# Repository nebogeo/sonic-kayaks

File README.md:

Sonic Kayak
===========

Originally based on the [Sonic Bikes](https://github.com/sonicbikes/)
system, a Raspberry Pi based citizen science project where kayaks
become musical & scientific instruments for investigating the marine
world.

We've added new sensors for citizen science data collection purposes:

* Thermometer
* Air pollution (particulate matter)
* Custom turbidity sensor
* Hydrophone

The system uses Pure Data for live audio sonification.

See the [Wiki](https://github.com/fo-am/sonic-kayaks/wiki) for full documentation on how to build a Sonic Kayak.

More installation instructions for the Raspberry Pi can be found here:
https://github.com/sonicbikes/sonic-bike-init

Hardware License
----------------

Sonic Kayak sensors, electronics designs and waterproofing systems Copyright (C) 2020 FoAM Kernow

[CERN Open Hardware Licence Version 2 - Strongly Reciprocal](https://ohwr.org/project/cernohl/wikis/Documents/CERN-OHL-version-2)

(See HWLICENSE)

Software License
------------------
Swamp Bike Opera embedded system for Kaffe Matthews <br>
Copyright (C) 2012 Wolfgang Hauptfleisch, Dave Griffiths<br>
Later additions made by Tom Keene & Jairo Sanchez<br>
Sonic Kayak additions made by Amber Griffiths, Dave Griffiths,<br>
James P. Duffy, Federico Visi and Jo Garrett. 

This program is free software: you can redistribute it and/or modify<br>
it under the terms of the GNU General Public License as published by<br>
the Free Software Foundation, either version 3 of the License, or<br>
(at your option) any later version.<br>

This program is distributed in the hope that it will be useful,<br>
but WITHOUT ANY WARRANTY; without even the implied warranty of<br>
MERCHANTABILITY or FITNESS FOR A PARTICULAR PURPOSE.  See the<br>
GNU General Public License for more details.<br>

You should have received a copy of the GNU General Public License<br>
along with this program.  If not, see <http://www.gnu.org/licenses/>.

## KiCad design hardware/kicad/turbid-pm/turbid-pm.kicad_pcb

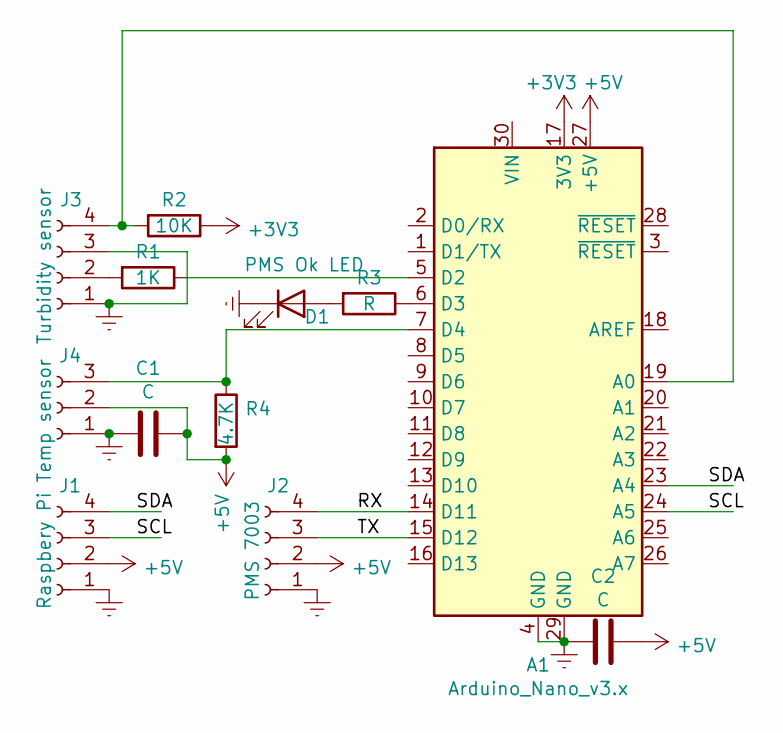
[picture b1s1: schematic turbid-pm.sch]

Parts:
A1: Arduino_Nano_v3.x; Arduino_Nano
C1, C2: C; C_Axial_L5.1mm_D3.1mm_P7.50mm_Horizontal
D1: PMS Ok LED; LED_D3.0mm_Clear
J1: Raspbery Pi; PinSocket_1x04_P2.54mm_Vertical
J2: PMS 7003; PinSocket_1x04_P2.54mm_Vertical
J3: Turbidity sensor; PinSocket_1x04_P2.54mm_Vertical
J4: Temp sensor; PinSocket_1x03_P2.54mm_Vertical
R1: 1K; R_Axial_DIN0207_L6.3mm_D2.5mm_P10.16mm_Horizontal
R2: 10K; R_Axial_DIN0207_L6.3mm_D2.5mm_P10.16mm_Horizontal
R3: R; R_Axial_DIN0207_L6.3mm_D2.5mm_P10.16mm_Horizontal
R4: 4.7K; R_Axial_DIN0207_L6.3mm_D2.5mm_P10.16mm_Horizontal

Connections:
+3V3: A1.17 (3V3), R2.1
+5V: A1.27 (+5V), C1.1, C2.1, J1.2, J2.2, J4.2, R4.2
/RX: A1.14 (D11), J2.4
/SCL: A1.24 (A5), J1.3
/SDA: A1.23 (A4), J1.4
/TX: A1.15 (D12), J2.3
Earth: A1.4 (GND), A1.29 (GND), C1.2, C2.2, D1.1 (K), J1.1, J2.1, J3.1, J3.3, J4.1
unnamed: A1.5 (D2), R1.1
unnamed: A1.6 (D3), R3.1
unnamed: A1.7 (D4), J4.3, R4.1
unnamed: A1.19 (A0), J3.4, R2.2
unnamed: D1.2 (A), R3.2
unnamed: J3.2, R1.2

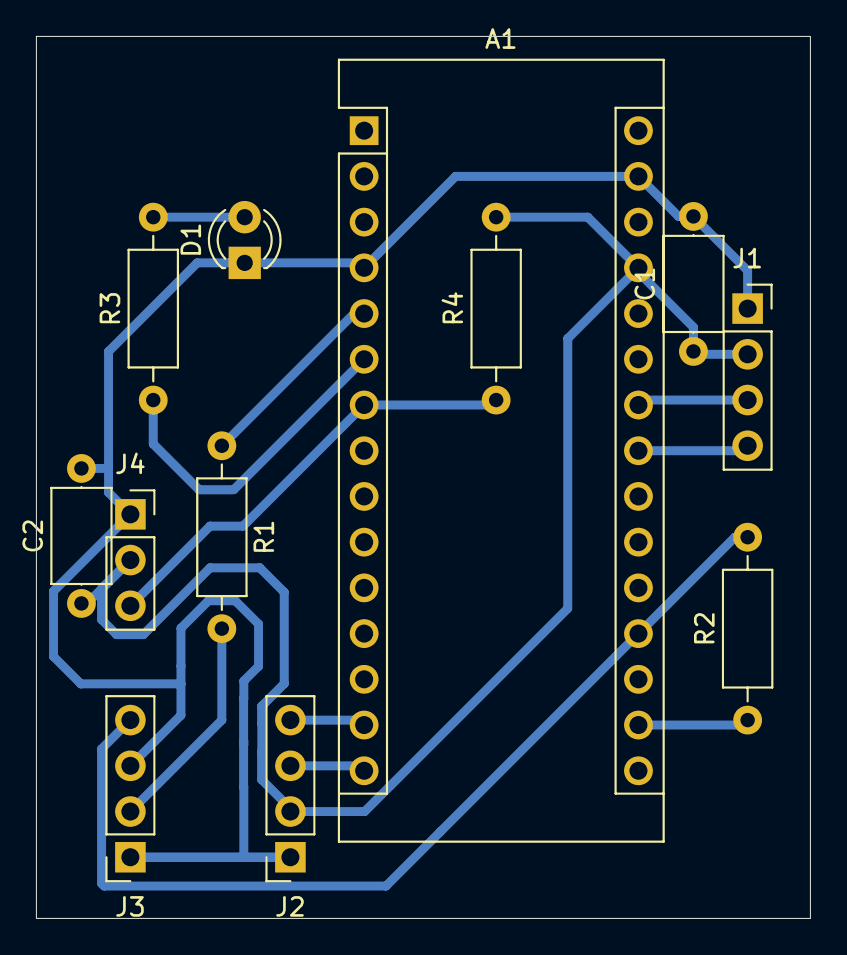
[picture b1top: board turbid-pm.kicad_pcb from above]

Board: 2 copper layers, 43.0 x 49.0 mm, 12 parts (0 on the bottom side), 13 nets.

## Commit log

2011-11-14 xrun glitch reset
2016-06-22 re-added therm?
2016-06-22 sending gps over osc
2016-08-11 dynamic temp recalibration, using daemontools, removed log flush at the start
2018-03-13 python gps driver
2018-03-13 adjusted code to work with actual GPS device input
2018-03-13 added checks for NMEA mode
2018-03-14 added more comments and updated system calls to use subprocess
2018-03-14 added if statement to deal with nodata. added status codes
2018-03-14 tidying code and comments, got rid of chdir
2018-03-14 new gps device driver
2018-04-18 modified to state machine style script
2018-04-19 time formatting now deals with single digit numbers
2018-04-19 tidy up comments, turn off state printer
2018-04-19 trimmed down fifo function
2018-04-19 logging adopts system datetime in same format as GPS. Also records thermometer ID in log
2018-04-20 changed location of therm script
2018-04-20 fixed formatting of lat/lon data
2018-04-24 the start of geojson creation scripts
2018-04-25 functionsed log formatting
2018-04-25 tidy
2018-04-26 change gps log name
2018-05-01 adding pictures for wiki illustration
2018-05-01 crop picture
2018-05-02 testing
2018-05-09 sound card testing graph
2018-05-09 pulling out frequencies of interest using python
2018-05-10 formatted output and adding correction file
2018-05-10 remove unceccessary modules
2018-05-10 expanded comments
2018-05-10 fixed path refs
2018-05-10 fix numpy/np ref
2018-05-22 converting hydrophone data to geojson, first go - incomplete
2018-05-23 initial working script
2018-05-23 linestring creator
2018-05-24 working geojson function
2018-05-24 tidy up
2018-05-25 tidying up
2018-05-31 added nofix to fifo function for new sound debug
2018-05-31 added pure data patches, need to be on the usb stick
2018-05-31 fixed startup issues
2018-06-05 add json import
2018-06-05 leaflet mapping stuff
2018-06-05 corrected data location
2018-06-05 added shellscript to run all geojson processing
2019-05-28 updated to work with ublox m8n
2019-08-20 added turbidity driver
2019-08-26 added combined sensor reader
2019-08-26 added avr firmware for turbidity and temperature sensors
2019-09-04 added a bunch of gps testing scripts
2019-09-04 added pic
2019-09-04 added gps sniffer
2019-10-01 updated gps script to use serial with a set baud rate and select between usb and uart devices, also tabs to spaces
2019-10-08 bluetooth reconnections and fixed 100% cpu problem in therm.py
2019-10-14 renamed and cleaned up
2019-10-14 moved audio restarter
2019-10-15 gps fixes and satellite sonification
2019-12-02 added electronics mount
2020-02-10 updated the pd scripts
2020-03-23 added particulate matter sensor driver
2020-03-23 pmatter script logging to the right place
2020-03-27 added particulate matter sonification, and fixed bug in gps sonification
2020-04-24 added arduino code for turbidity and particulate matter air sensor, and mapping for air test
2020-04-24 moving things around
2020-04-24 added kicad bits
2020-04-25 stream reader for pm sensor
2020-04-27 added new arduino driver
2020-04-27 added 3d print source
2020-04-27 added thermometers to the arduino - just in case...
2020-05-04 pm stream tested and working
2020-05-04 rename and lost files
2020-05-06 added wobble classifier
2020-05-07 restricted wobble classifier to rise/fall and added pd file export
2020-05-07 added some mapping things left behind
2020-05-08 aggregated sensor data and reading in PD
2020-05-11 added synth and sample sonification patches
2020-05-12 granular sonification tests
2020-05-13 sorting things out, added samples
2020-05-13 three sonifications done
2020-05-15 more sonification changes, fake sensor generator
2020-05-28 Added Modular_Sonifcation_Lab
2020-05-28 Fixed no sound after loading sound file
2020-06-02 stuff for sonification videos
2020-06-12 air pollution reading from arduino and multiple sensor support
2020-06-22 added temperature read to arduino code and added stripboard fritzing project
2020-06-24 docs
2020-06-24 resize
2020-06-24 added stripboard photos
2020-06-24 new pic
2020-06-25 added therm pic
2020-06-25 crop
2020-06-25 added turbidity pic
2020-06-25 turb cable pics
2020-06-25 air pm doc pics
2020-06-26 image tweak
2020-06-26 pi connection doc image added
2020-06-26 image trim
2020-07-01 new arduino reader with temp and states to pd
2020-07-01 fixed classifier bug2
2020-07-20 more error reporting and startup fix for hydrophone
2020-07-20 more error propagation
2020-07-20 new firmware and docs
2020-07-20 added hydrophone doc image
2020-07-27 lotsa bits
2020-08-03 new thresholds
2020-09-14 adding final action bits
2020-09-16 stl mixup
2020-09-25 added sound analysis
2020-09-28 added james' code
2020-09-28 clearing up missing files
2020-09-28 schematic fix
2020-12-14 added cap to stripboard diagram
2021-01-26 Create LICENSE
2021-01-26 Update LICENSE
2021-01-26 added hardware license
2021-01-26 tweaked readme
2021-04-08 Add files via upload
    This is a revised prototype version of the turbidity tube for strapping directly under the hull of a kayak. There are spaces for two 2cm webbing straps to pass through to hold the tube onto the kayak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
